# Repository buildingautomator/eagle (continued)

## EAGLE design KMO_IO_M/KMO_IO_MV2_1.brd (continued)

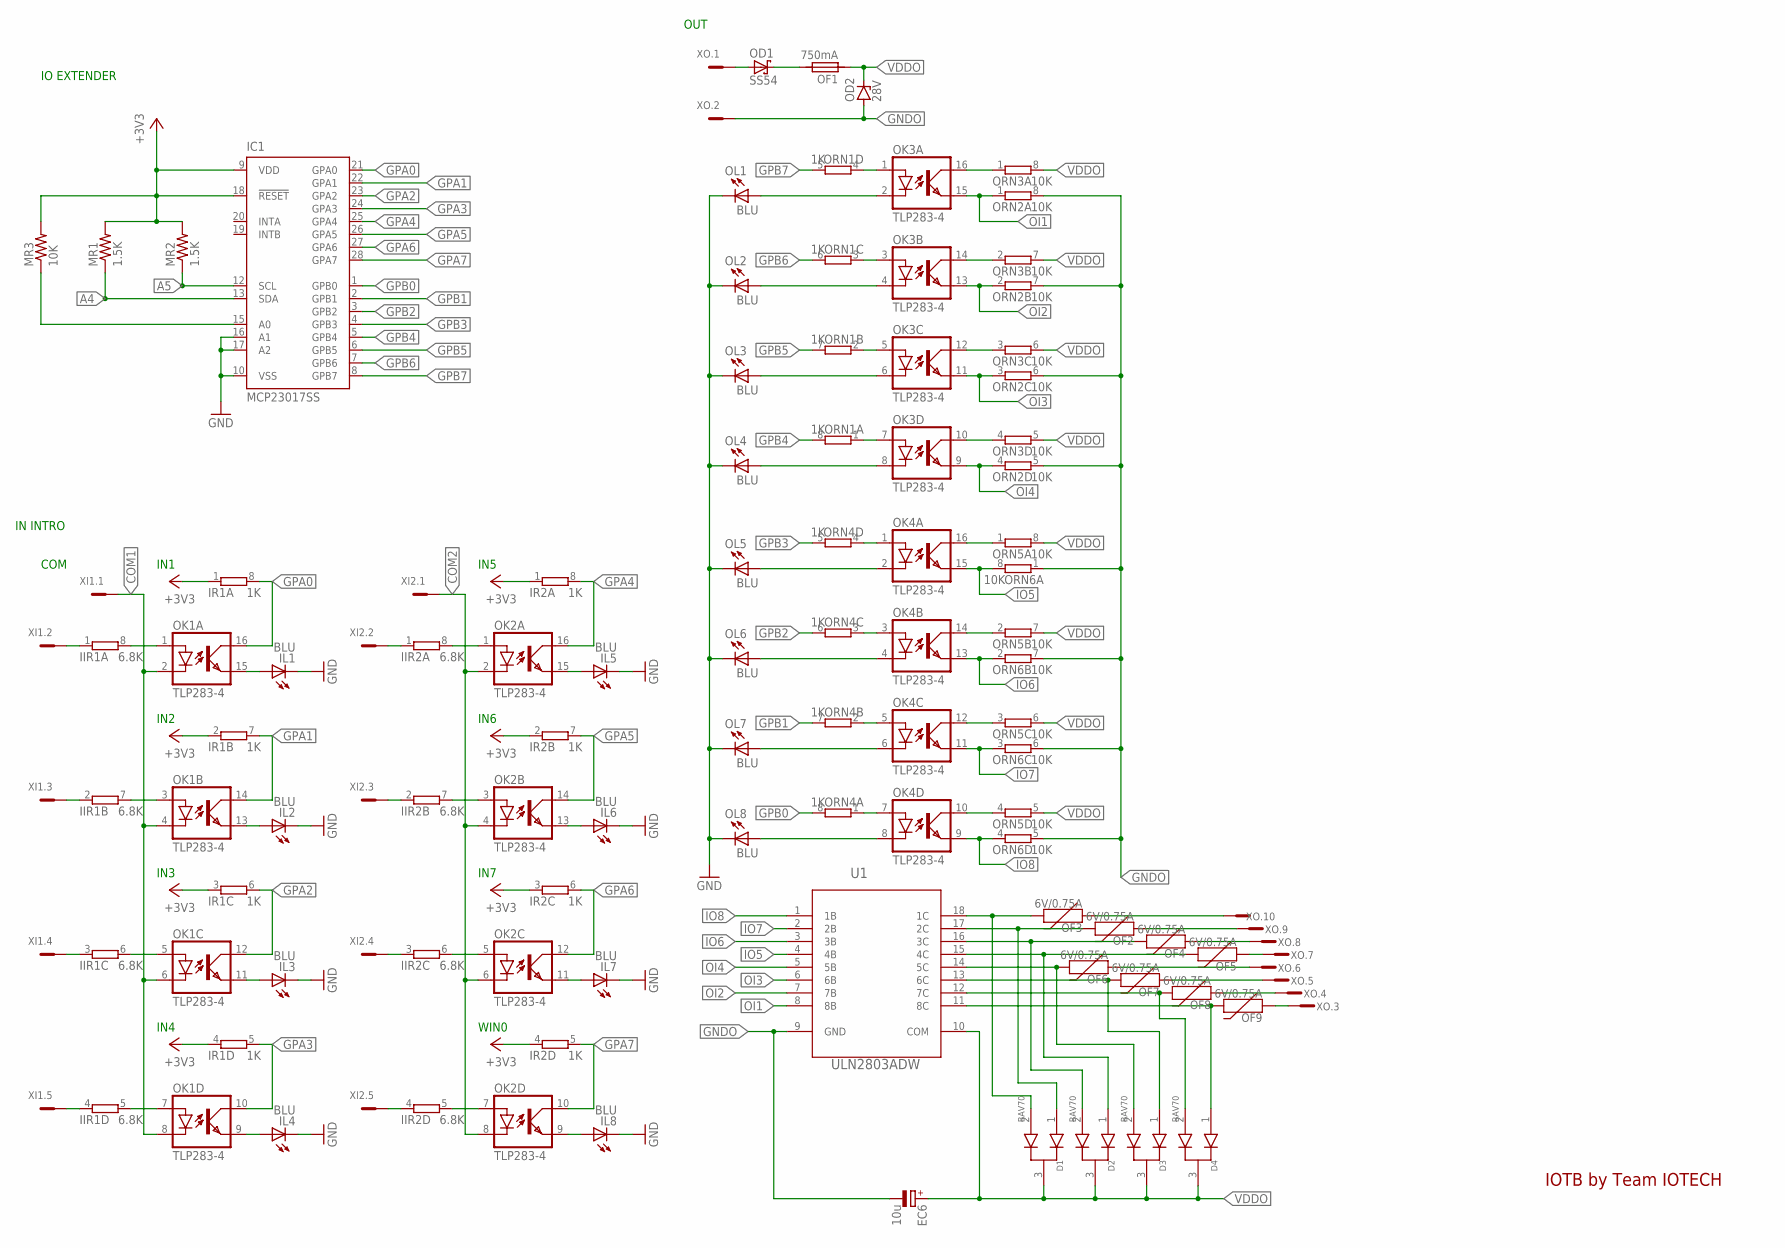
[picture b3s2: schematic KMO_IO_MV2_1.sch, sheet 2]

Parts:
D1, D2, D3, D4: BAV70; SOT-23-3
EC6: 10u; CT3216
IC1: MCP23017SS; SSOP28
IIR1, IIR2: 6.8K; 0603-ARV
IL1, IL2, IL3, IL4, IL5, IL6, IL7, IL8: BLU; CHIP-LED0805
IR1, IR2: 1K; 0603-ARV
MR1, MR2: 1.5K; 0805
MR3: 10K; 0805
OD1: SS54; SMB
OD2: 28V; SMB
OF1: 750mA; 1820
OF2, OF3, OF4, OF5, OF6, OF7, OF8, OF9: 6V/0.75A; 1206
OK1, OK2, OK3, OK4: TLP283-4; MINI-FLAT-16
OL1, OL2, OL3, OL4, OL5, OL6, OL7, OL8: BLU; CHIP-LED0805
ORN1, ORN4: 1K; 0603-ARV
ORN2, ORN3, ORN5, ORN6: 10K; 0603-ARV
U1: ULN2803ADW; SOIC127P1030X265-18N
XI1, XI2: MC5
XO: MC10

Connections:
+3V3: IC1.9 (VDD), IC1.18 (!RESET), IR1.1, IR1.2 (1), IR1.3 (1), IR1.4 (1), IR2.1, IR2.2 (1), IR2.3 (1), IR2.4 (1), MR1.2, MR2.2, MR3.2; also elsewhere on the board
A4: IC1.13 (SDA), MR1.1; also elsewhere on the board
A5: IC1.12 (SCL), MR2.1; also elsewhere on the board
COM1: OK1.2 (C), OK1.4 (C), OK1.6 (C), OK1.8 (C), XI1.1
COM2: OK2.2 (C), OK2.4 (C), OK2.6 (C), OK2.8 (C), XI2.1
GND: IC1.10 (VSS), IC1.16 (A1), IC1.17 (A2), IL1.C, IL2.C, IL3.C, IL4.C, IL5.C, IL6.C, IL7.C, IL8.C, OL1.C, OL2.C, OL3.C, OL4.C, OL5.C, OL6.C, OL7.C, OL8.C; also elsewhere on the board
GNDO: EC6.-, OD2.A, ORN2.5 (2), ORN2.6 (2), ORN2.7 (2), ORN2.8 (2), ORN6.1, ORN6.5 (2), ORN6.6 (2), ORN6.7 (2), U1.9 (GND), XO.2
GPA0: IC1.21 (GPA0), IR1.8 (2), OK1.16 (COL)
GPA1: IC1.22 (GPA1), IR1.7 (2), OK1.14 (COL)
GPA2: IC1.23 (GPA2), IR1.6 (2), OK1.12 (COL)
GPA3: IC1.24 (GPA3), IR1.5 (2), OK1.10 (COL)
GPA4: IC1.25 (GPA4), IR2.8 (2), OK2.16 (COL)
GPA5: IC1.26 (GPA5), IR2.7 (2), OK2.14 (COL)
GPA6: IC1.27 (GPA6), IR2.6 (2), OK2.12 (COL)
GPA7: IC1.28 (GPA7), IR2.5 (2), OK2.10 (COL)
GPB0: IC1.1 (GPB0), ORN4.8 (2)
GPB1: IC1.2 (GPB1), ORN4.7 (2)
GPB2: IC1.3 (GPB2), ORN4.6 (2)
GPB3: IC1.4 (GPB3), ORN4.5 (2)
GPB4: IC1.5 (GPB4), ORN1.8 (2)
GPB5: IC1.6 (GPB5), ORN1.7 (2)
GPB6: IC1.7 (GPB6), ORN1.6 (2)
GPB7: IC1.8 (GPB7), ORN1.5 (2)
IO5: OK4.15 (EMIT), ORN6.8 (2), U1.4 (4B)
IO6: OK4.13 (EMIT), ORN6.2 (1), U1.3 (3B)
IO7: OK4.11 (EMIT), ORN6.3 (1), U1.2 (2B)
IO8: OK4.9 (EMIT), ORN6.4 (1), U1.1 (1B)
unnamed: OD1.A, XO.1
unnamed: IC1.15 (A0), MR3.1
unnamed: OD1.C, OF1.2
unnamed: OF3.1, XO.10
unnamed: D1.1, OF2.2, U1.17 (2C)
unnamed: OK3.1 (A), ORN1.4 (1)
unnamed: IL1.A, OK1.15 (EMIT)
unnamed: IIR1.1, XI1.2
unnamed: IL2.A, OK1.13 (EMIT)
unnamed: IL3.A, OK1.11 (EMIT)
unnamed: IL4.A, OK1.9 (EMIT)
unnamed: IL5.A, OK2.15 (EMIT)
unnamed: IL6.A, OK2.13 (EMIT)
unnamed: IL7.A, OK2.11 (EMIT)
unnamed: IIR1.2 (1), XI1.3
unnamed: IIR1.8 (2), OK1.1 (A)
unnamed: IIR1.7 (2), OK1.3 (A)
unnamed: IIR1.6 (2), OK1.5 (A)
unnamed: IIR1.5 (2), OK1.7 (A)
unnamed: IIR1.3 (1), XI1.4
unnamed: IIR1.4 (1), XI1.5
unnamed: OK3.3 (A), ORN1.3 (1)
unnamed: IIR2.1, XI2.2
unnamed: IIR2.8 (2), OK2.1 (A)
unnamed: IIR2.2 (1), XI2.3
unnamed: IIR2.7 (2), OK2.3 (A)
unnamed: IIR2.3 (1), XI2.4
unnamed: IIR2.6 (2), OK2.5 (A)
unnamed: IIR2.4 (1), XI2.5
unnamed: IIR2.5 (2), OK2.7 (A)
unnamed: IL8.A, OK2.9 (EMIT)
unnamed: OK3.5 (A), ORN1.2 (1)
unnamed: OK3.7 (A), ORN1.1
unnamed: D1.2, OF3.2, U1.18 (1C)
unnamed: OK3.16 (COL), ORN3.1
unnamed: D2.2, OF4.2, U1.16 (3C)
unnamed: D2.1, OF5.2, U1.15 (4C)
unnamed: OF2.1, XO.9
unnamed: OF4.1, XO.8
unnamed: OK3.14 (COL), ORN3.2 (1)
unnamed: OF5.1, XO.7
unnamed: OF6.1, XO.6
unnamed: OK3.12 (COL), ORN3.3 (1)
unnamed: D3.1, OF7.2, U1.13 (6C)
unnamed: OK3.10 (COL), ORN3.4 (1)
unnamed: D4.2, OF8.2, U1.12 (7C)
unnamed: OK3.2 (C), OL1.A
unnamed: OK3.4 (C), OL2.A
unnamed: OK3.6 (C), OL3.A
unnamed: OK3.8 (C), OL4.A
unnamed: D4.1, OF9.2, U1.11 (8C)
unnamed: D3.2, OF6.2, U1.14 (5C)
unnamed: OF7.1, XO.5
unnamed: OF8.1, XO.4
unnamed: OF9.1, XO.3
unnamed: OK4.1 (A), ORN4.4 (1)
unnamed: OK4.3 (A), ORN4.3 (1)
unnamed: OK4.5 (A), ORN4.2 (1)
unnamed: OK4.7 (A), ORN4.1
unnamed: OK4.16 (COL), ORN5.1
unnamed: OK4.14 (COL), ORN5.2 (1)
unnamed: OK4.12 (COL), ORN5.3 (1)
unnamed: OK4.10 (COL), ORN5.4 (1)
unnamed: OK4.2 (C), OL5.A
unnamed: OK4.4 (C), OL6.A
unnamed: OK4.6 (C), OL7.A
unnamed: OK4.8 (C), OL8.A
OI1: OK3.15 (EMIT), ORN2.1, U1.8 (8B)
OI2: OK3.13 (EMIT), ORN2.2 (1), U1.7 (7B)
OI3: OK3.11 (EMIT), ORN2.3 (1), U1.6 (6B)
OI4: OK3.9 (EMIT), ORN2.4 (1), U1.5 (5B)
VDDO: D1.3, D2.3, D3.3, D4.3, EC6.+, OD2.C, OF1.1, ORN3.5 (2), ORN3.6 (2), ORN3.7 (2), ORN3.8 (2), ORN5.5 (2), ORN5.6 (2), ORN5.7 (2), ORN5.8 (2), U1.10 (COM)

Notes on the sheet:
IOTB by Team IOTECH
IN INTRO
IN1
IN2
IN3
IN4
IN5
IN6
IN7
WIN0
COM
OUT
IO EXTENDER

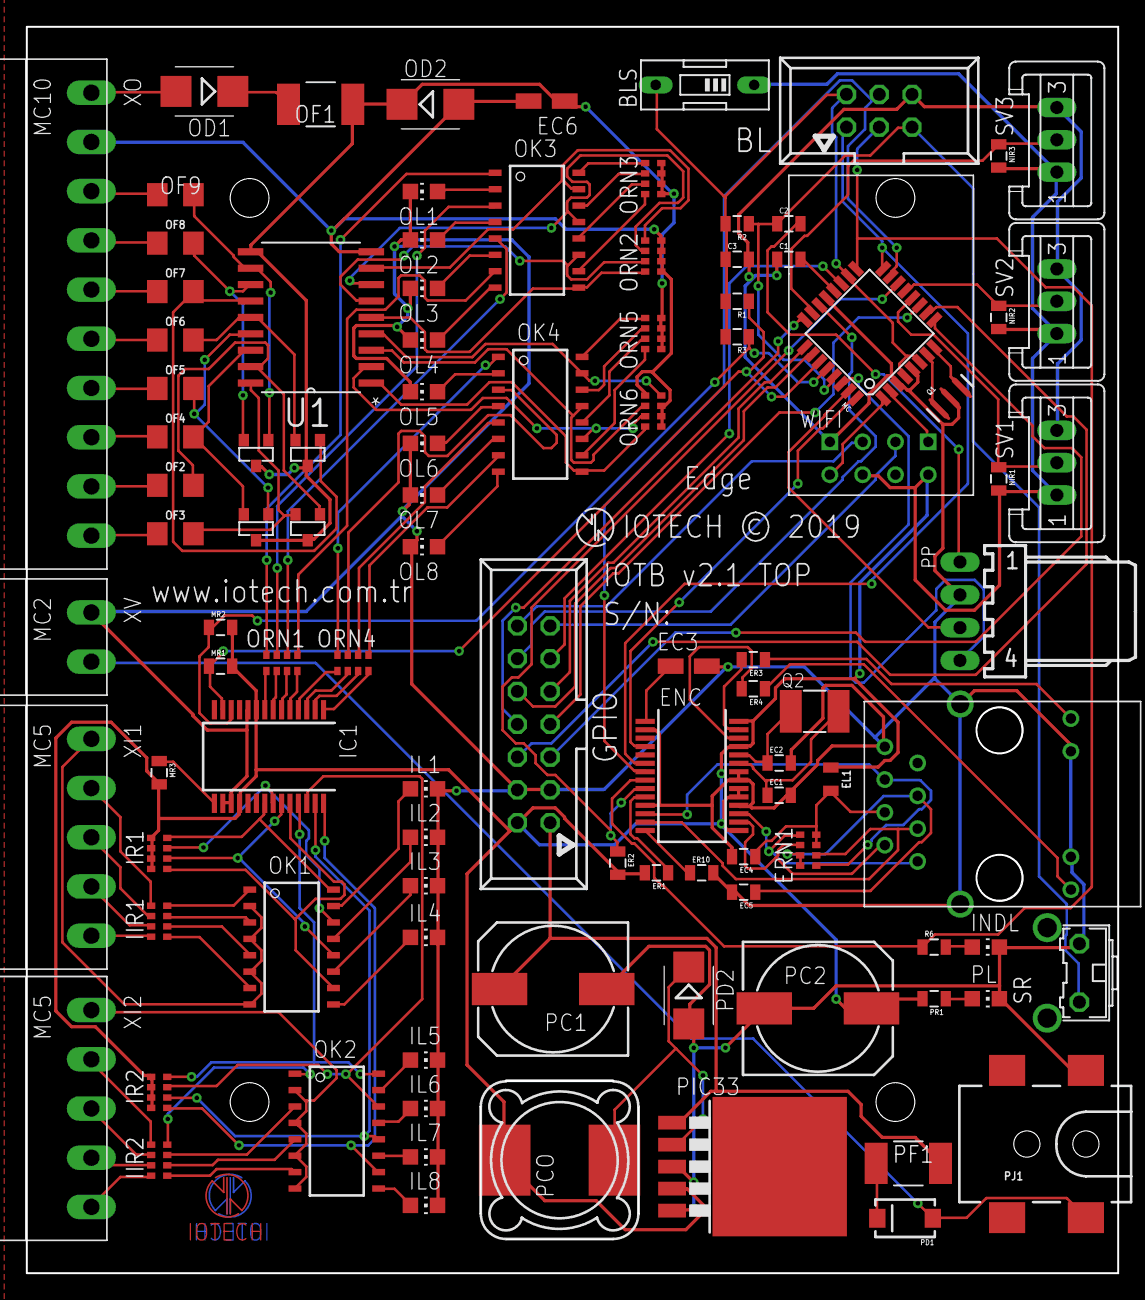
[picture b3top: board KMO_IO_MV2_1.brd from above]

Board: 2 copper layers, 84.5 x 96.5 mm, 104 parts (1 on the bottom side), 148 nets.

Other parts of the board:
U$1, U$4: IOTECH_COPPER_W_TEXT

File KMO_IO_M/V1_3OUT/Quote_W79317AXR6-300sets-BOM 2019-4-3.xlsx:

300sets | total | remark | Quantity | Part | Value | Device | Package | Description MF MPN OC_FARNELL OC_NEWARK PROD_ID SF_ID SPICEPREFIX VALUE
 | 0 | pls offer correct part number | 1 | BL | 057-006-1 | 057-006-1 | 057-006-1 | CONNECTOR unknown unknown
 | 0 | pls offer part number | 1 | BLS |  | SW_DIP-1 | EDG-01 | DIP SWITCH
0.033 | 9.9 |  | 1 | C1 | 100nF | CAP0805 | 805 | Capacitor
0.033 | 9.9 |  | 1 | C2 | 100nF | CAP0805 | 805 | Capacitor
0.033 | 9.9 |  | 1 | C3 | 100nF | CAP0805 | 805 | Capacitor
0.0088 | 2.64 |  | 1 | EC1 | 18p | CAP0805 | 805 | Capacitor
0.0088 | 2.64 |  | 1 | EC2 | 18p | CAP0805 | 805 | Capacitor
0.132 | 39.6 | we offer TANT 10UF 16V A3216,OK? | 1 | EC3 | 10u | CPOL-EUCT3216 | CT3216 | POLARIZED CAPACITOR, European symbol C
0.0088 | 2.64 |  | 1 | EC4 | 10n | CAP0805 | 805 | Capacitor
0.0088 | 2.64 |  | 1 | EC5 | 10n | CAP0805 | 805 | Capacitor
 | 0 | pls offer part number | 1 | EL1 | 10礖 | INDUCTOR-0805-3.3UH | 805 | Inductors NDUC-13076 3.3礖/?0%/450mA
2.31 | 693 | we offer ENC28J60/SS SSOP28,OK? | 1 | ENC | ENC28J60-SSOP | ENC28J60-SSOP | SSOP28 | Microchip 10Mbit Eth. contoller with SPI interface
0.0088 | 2.64 |  | 1 | ER1 | 10k | RESISTOR0805-RES | 805 | Resistor
0.0088 | 2.64 |  | 1 | ER2 | 10k | RESISTOR0805-RES | 805 | Resistor
0.0088 | 2.64 |  | 1 | ER3 | 1k | RESISTOR0805-RES | 805 | Resistor
0.0088 | 2.64 |  | 1 | ER4 | 1k | RESISTOR0805-RES | 805 | Resistor
0.0088 | 2.64 | do not have 50R ,we offer 49.9R,OK? | 1 | ER6 | 50R | RESISTOR0805-RES | 805 | Resistor
0.0088 | 2.64 | do not have 50R ,we offer 49.9R,OK? | 1 | ER7 | 50R | RESISTOR0805-RES | 805 | Resistor
0.0088 | 2.64 | do not have 50R ,we offer 49.9R,OK? | 1 | ER8 | 50R | RESISTOR0805-RES | 805 | Resistor
0.0088 | 2.64 | do not have 50R ,we offer 49.9R,OK? | 1 | ER9 | 50R | RESISTOR0805-RES | 805 | Resistor
0.0088 | 2.64 | we offer LTST-C170TBKT blue,OK? | 1 | ER10 | 2.7K | RESISTOR0805-RES | 805 | Resistor
0.0385 | 11.55 | we offer LTST-C170TBKT blue,OK? | 1 | IL1 | BLU | LEDCHIP-LED0805 | CHIP-LED0805 | LED
0.0385 | 11.55 | we offer LTST-C170TBKT blue,OK? | 1 | IL2 | BLU | LEDCHIP-LED0805 | CHIP-LED0805 | LED
0.0385 | 11.55 | we offer LTST-C170TBKT,blue,OK? | 1 | IL3 | BLU | LEDCHIP-LED0805 | CHIP-LED0805 | LED
0.0385 | 11.55 | we offer LTST-C170TBKT,blue,OK? | 1 | IL4 | BLU | LEDCHIP-LED0805 | CHIP-LED0805 | LED
0.0385 | 11.55 | we offer LTST-C170TBKT blue,OK? | 1 | IL5 | BLU | LEDCHIP-LED0805 | CHIP-LED0805 | LED
0.0385 | 11.55 | we offer LTST-C170TBKT blue,OK? | 1 | IL6 | BLU | LEDCHIP-LED0805 | CHIP-LED0805 | LED
0.0385 | 11.55 | we offer LTST-C170TBKT blue,OK? | 1 | IL7 | BLU | LEDCHIP-LED0805 | CHIP-LED0805 | LED
0.0385 | 11.55 | we offer LTST-C170TBKT blue,OK? | 1 | INDL | BLU | LEDCHIP-LED0805 | CHIP-LED0805 | LED
0.0088 | 2.64 |  | 1 | IR | 10K | RESISTOR0805-RES | 805 | Resistor
0.0088 | 2.64 |  | 1 | IR1 | 1K | RESISTOR0805-RES | 805 | Resistor
0.0088 | 2.64 |  | 1 | IR2 | 1K | RESISTOR0805-RES | 805 | Resistor
0.0088 | 2.64 |  | 1 | IR3 | 1K | RESISTOR0805-RES | 805 | Resistor
0.0088 | 2.64 |  | 1 | IR4 | 1K | RESISTOR0805-RES | 805 | Resistor
0.0088 | 2.64 |  | 1 | IR5 | 1K | RESISTOR0805-RES | 805 | Resistor
0.0088 | 2.64 |  | 1 | IR6 | 1K | RESISTOR0805-RES | 805 | Resistor
0.0088 | 2.64 |  | 1 | IR7 | 1K | RESISTOR0805-RES | 805 | Resistor
 | 0
 | 0
 | 0
0.0385 | 11.55 | 1N4007 SMA | 1 | OD1 | M7 | DIODESMA | SMA-DIODE | Diode
0.0385 | 11.55 | 1N4007 SMA | 1 | OD2 | M7 | DIODESMA | SMA-DIODE | Diode
0.0385 | 11.55 | 1N4007 SMA | 1 | OD3 | M7 | DIODESMA | SMA-DIODE | Diode
0.0385 | 11.55 | we offer LTST-C170KSKT yellow,OK? | 1 | OL1 | YLW | LEDCHIP-LED0805 | CHIP-LED0805 | LED
0.0385 | 11.55 | we offer LTST-C170KSKT yellow,OK? | 1 | OL2 | YLW | LEDCHIP-LED0805 | CHIP-LED0805 | LED
0.0385 | 11.55 | we offer LTST-C170KSKT yellow,OK? | 1 | OL3 | YLW | LEDCHIP-LED0805 | CHIP-LED0805 | LED
 | 0 | out of stock,pls advise replacement? | 1 | OQ1 | IRF3707S | IRF3704S | D2PACK | SMPS MOSFET
 | 0 | out of stock,pls advise replacement? | 1 | OQ2 | IRF3707S | IRF3704S | D2PACK | SMPS MOSFET
 | 0 | out of stock,pls advise replacement? | 1 | OQ3 | IRF3707S | IRF3704S | D2PACK | SMPS MOSFET
0.0088 | 2.64 |  | 1 | OR1 | 1K | RESISTOR0805-RES | 805 | Resistor
0.0088 | 2.64 |  | 1 | OR2 | 1K | RESISTOR0805-RES | 805 | Resistor
0.0088 | 2.64 |  | 1 | OR3 | 1K | RESISTOR0805-RES | 805 | Resistor
 | 0 | pls offer part number | 1 | PC1 | 470uf 25v | CPOL-EU140CLH-1010 | 140CLH-1010 | POLARIZED CAPACITOR, European symbol C
 | 0 | pls offer part number | 1 | PC2 | 220uf 50v | CPOL-EU140CLH-1010 | 140CLH-1010 | POLARIZED CAPACITOR, European symbol C
1.485 | 445.5 | MSS1260-224KLD | 1 | PCO | 220 uh | MSS1260 | MSS1260 | SMT Power Inductor
0.055 | 16.5 | 1N4007 | 1 | PD1 | M7 | DIODESMA | SMA-DIODE | Diode
0.11 | 33 |  | 1 | PD2 | SS54 | SCHOTTKY-DIODESMD | SMB | Schottky Diode
 | 0 | pls offer correct part number | 1 | PF1 | 1A | SIBA194600 | 1820 | SIBA PTC-Fuses, Series 194600, 1812 (4.5 3.2)mm
1.76 | 528 | LM2596S-ADJ/NOPB | 1 | PIC33 | LM2596S | LM2596S | TO263-5 | SIMPLE SWITCHER?Power Converter 150 kHz 3A Step-Down Voltage Regulator NATIONAL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
 | 0 | pls offer part number | 1 | PJ1 | POWER_JACKTOE | POWER_JACKTOE | POWER_JACK_SMD_OVERPASTE_TOE | Power Jack Connector CONN-08106 PRT-12748
0.0385 | 11.55 | we offer LTST-C170KGKT green,OK? | 1 | PL | GRN | LEDCHIP-LED0805 | CHIP-LED0805 | LED
 | 0 | pls offer correct part number | 1 | PP | 22-05-7048-04 | 22-05-7048-04 | 2007100 | CONNECTOR MOLEX unknown unknown 90 Degree horizontal
0.0088 | 2.64 |  | 1 | PR1 | 1k | RESISTOR0805-RES | 805 | Resistor
 | 0 | pls offer part number | 1 | Q1 | 8MHz | RESONATOR1:1 | RESONATOR-SMD-1:1 | Resonator
 | 0 | pls offer part number | 1 | Q2 | 25MHz | KX-9B | 5.0X3.2_2 | Quartz Crystals (MHz) SMD:
 | 0
0.0088 | 2.64 |  | 1 | R2 | 10K | RESISTOR0805-RES | 805 | Resistor
 | 0
0.0088 | 2.64 |  | 1 | R6 | 1k | RESISTOR0805-RES | 805 | Resistor
0.275 | 82.5 | we offer B3F-3100,pls confirm? | 1 | SR |  | 31-XX | B3F-31XX | OMRON SWITCH B3F-3100 959704 36M3582
 | 0 | pls offer part number | 1 | SV1 |  | S03P | S03P | AMP MT CONNECTOR 90 Degree horizontal
 | 0 | pls offer part number | 1 | SV2 |  | S03P | S03P | AMP MT CONNECTOR 90 Degree horizontal
 | 0 | pls offer part number | 1 | SV3 |  | S03P | S03P | AMP MT CONNECTOR 90 Degree horizontal
1.342 | 402.6 |  | 1 | U$2 | HR911105A | HR911105A | RJ45
1.485 | 445.5 | we offer ATMEGA328P-AU ,pls confirm? | 1 | U1 | ATMEGA328 | ATMEGA168 | TQFP32-08
 | 0 |  | 1
0.0385 | 11.55 | we offer LTST-C170TBKT blue? | 1 | WIL0 | BLU | LEDCHIP-LED0805 | CHIP-LED0805 | LED
0.0385 | 11.55 | we offer LTST-C170TBKT blue,OK? | 1 | WIL2 | BLU | LEDCHIP-LED0805 | CHIP-LED0805 | LED
0.0088 | 2.64 |  | 1 | WIR0 | 1K | RESISTOR0805-RES | 805 | Resistor
0.0088 | 2.64 |  | 1 | WIR2 | 1K | RESISTOR0805-RES | 805 | Resistor
 | 0 | pls offer part number or product link? | 1 | X1 | MC3 | MC3 | MC3 | Mini-Combicon 3.81mm horizontal 3-polig
 | 0 | pls offer part number or product link? | 1 | XI | MC10 | MC10 | MC10 | Mini-Combicon 3.81mm horizontal 10-polig
 | 0 | pls offer part number or product link? | 1 | XO | MC6 | MC6 | MC6 | Mini-Combicon 3.81mm horizontal 6-polig
 | 2988.81
